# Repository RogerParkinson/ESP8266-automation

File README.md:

ESP8266-automation
==

Code and circuitry to support simple event driven signaling from remote sensors (ESP8266) to a server (BeagleBone) over WIFI. The remote sensors detect an n/o switch being closed and they send a message to the server which decides what to do with it. Normally it logs it and there is a web page to query the log. But for some messages it will sound a chime. The remote sensors also send a battery status when they power up.

I could have used some public service to manage the logging, and eliminated the Beaglebone, but I tend to resist exposing home automation events to public services and I had the Beaglebone already acting as a file server. I'm not sure I would have easily managed the chime from a public service, though probably another ESP listening on the network could do it.

Remote Switch
=

The remote sensors use an ESP8266-01. Use 3xAA batteries as the power supply and any convenient ssensor. A simple mercury switch is fine but I did something more complicated in the one shown in the following image.

The black box is an AA battery holder containing 3 NiMH rechargeable AA batteries. The wires from that are connected to the purple board, the one I designed, and at the other end the ESP8266-01 is plugged in.

The purple board has a test button on it which forces it to send a message. It also has a pair of grey wires going to the n/o switch. A slightly simpler configuration is to solder a mercury switch directly to those connections and make the unit standalone. If you do that make sure you adjust the way the mercury switch is lying to ensure it is open until disturbed. I use that configuration on vermin traps.

This configuration, however, is for my gate. I have a wooden gate on my drive and I rigged a slider on it using some fencing wire, bits of copper and a piece of dowel.

On the right hand side you can see two grey wires. The lower one is fencing wire, quite stiff. That is attached to the gate and provides the movement. The other wire is electrical and is the other end of one of the wires you saw earlier. Its mate is attached to the piece of copper wrapped around the nail. Driven by the fencing wire the dowel slides back and forth and the copper sleeve on the dowel touches the copper on the nail, making the conection. That triggers the ESP to send a signal with it's internal serial number (see the code) to the Beaglebone over WIFI.

I have a similar arrangement on my mailbox, but that is triggered by a mercury switch positioned so that my mail lady's vehicle (she comes in a car because we're rural) runs over a buried metal rod and that jiggles the mercury switch envough to trigger the unit there.
  
The project board is defined in the Eagle files under the ESP8266TX directory. There are connectors on the board for VCC and GND as well as two for the Switch (eg the mercury switch). This switch earths the CH_PD pin on the ESP which will wake it from deep sleep. You can solder the ESP onto it directly but I prefer to use [these connectors](https://www.aliexpress.com/item/50-pcs-4P-4pin-Female-Single-Row-Straight-Header-Strip-Socket-Connector-Pitch-2-54mm/32442780670.html) so I can unplug the ESP if I need to reflash it. Flash the ESP with the code in RemoteSwitch.ino [details here](https://madurasoftware.com/blog/esp8266-01-flashing-tool). There is a note in the top of the ino file explaining how to specify your own WIFI network.

You can order the board ($4 for 3) from [OSH PARK]

<a href="https://www.oshpark.com/shared_projects/U9vJnOx3"></img></a>

It is worth while removing the red LED from the ESP because it runs all the time and reduces battery life. Just grab it with some small pliers and pull.

BeagleBone
=

The server is a Beaglebone running Nginx with some PHP scripts.

To set up the BeagleBone just install [Nginx](https://www.nginx.com/resources/wiki/start/topics/tutorials/install/#) and copy the php scripts from this project into `/usr/share/nginx/www`

If you want to use the chime then you need to wire up the BeagleBone like this:

And arrange for the `BeagleBone/startup/gpio60.sh` script to run at startup.

But better than a breadboard is to use a PCB. You'll find the one I used under BeagleBone/BBConnector in this project. And you can:

<a href="https://www.oshpark.com/shared_projects/K8a6LmDk"></img></a>

All this is doing is taking the 5V supply from the Beaglebone and applying it to the chimer. The chimer I had was part of an old alarm system I had lying around. It took 5V to sound a 'ding-dong' like a door bell. I'm controlling it with the transistor using a 3.3V signal from the Beaglebone GPIO. The transistor I used is a through hole one I happened to have.

Also create a file `/home/receiver/log.csv` and use chmod to make it writeable from anyone. This is the log file and it can be viewed by browsing to `http://<your BeagleBone>/printlog.php`. You should see something like this:

This shows mostly battery levels logged at startup, but the second entry shows the value in red, indicating it has dropped below 3000. The last entry is an actual event on the mailbox and was used to test the chime. I've since added a reboot and test button because sometimes I want to reboot the Beaglebone without trekking all the way upstairs to do it, and the test button triggers the chime without my having to go outside and swing on the gate.

To get the log showing the right names for the devices you need to edit the printlog.php file. Specifically this line:

`$sources = array("test" => "123","pond" => "16058556","backdoor" => "8442031", "mailbox" => "8425573");`

The values it is mapping against are the unique id of each ESP8266 obtained from the `ESP.getChipId()` call. If there is no mapping value the unmapped value appears in the log.

The same thing appears in the processevent.php file where the message source name is used to decide hether to sound the chime or not. You can customise this as needed.

To log the time properly you must ensure the BeagleBone's clock is set correctly. there is help on how to do this [here](http://derekmolloy.ie/automatically-setting-the-beaglebone-black-time-using-ntp/) however I had to use usr/sbin/ntp rather than usr/bin/ntp on my system.

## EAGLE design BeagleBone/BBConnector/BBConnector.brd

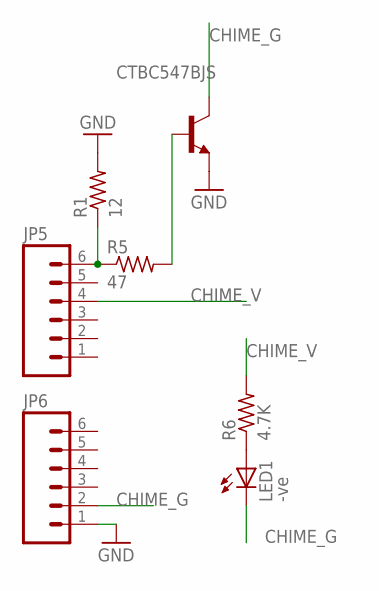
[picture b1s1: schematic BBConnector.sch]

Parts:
CTBC547BJS: 2N2222; TO92-EBC-OVAL
JP5, JP6: M06NO_SILK_YES_STOP; 1X06_NO_SILK_YES_STOP
LED1: -ve; CHIP-LED0603
R1: 12; R0603
R5: 47; R0603
R6: 4.7K; R0603

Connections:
CHIME_G: CTBC547BJS.C, JP6.2, LED1.C
CHIME_V: JP5.4, R6.2
GND: CTBC547BJS.E, JP6.1, R1.2
unnamed: JP5.6, R1.1, R5.1
unnamed: LED1.A, R6.1
unnamed: CTBC547BJS.B, R5.2

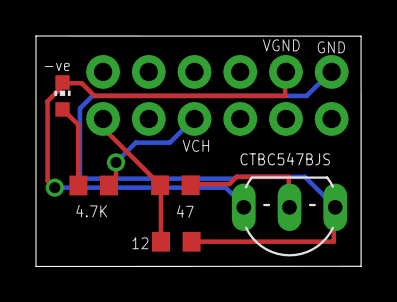
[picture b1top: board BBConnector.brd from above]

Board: 2 copper layers, 18.1 x 12.8 mm, 7 parts (0 on the bottom side), 6 nets.

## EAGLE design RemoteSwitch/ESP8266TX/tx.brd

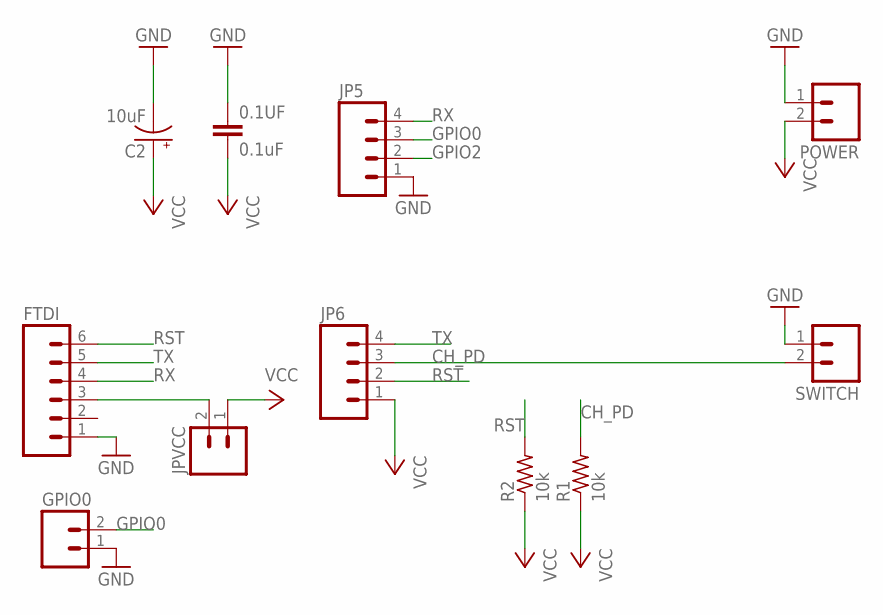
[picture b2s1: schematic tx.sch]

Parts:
0.1UF: 0.1uF; 0603-CAP
C2: 10uF; EIA6032
FTDI: M06LOCK; 1X06_LOCK
GPIO0: M02PTH; 1X02
JP5, JP6: M041X04_NO_SILK; 1X04_NO_SILK
JPVCC: M02PTH; 1X02
POWER: M02PTH; 1X02
R1, R2: 10k; R0805
SWITCH: M02PTH; 1X02

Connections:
CH_PD: JP6.3, R1.2, SWITCH.2
GND: 0.1UF.1, C2.P$2 (-), FTDI.1, GPIO0.1, JP5.1, POWER.1, SWITCH.1
GPIO0: GPIO0.2, JP5.3
GPIO2: JP5.2
unnamed: FTDI.3, JPVCC.2
RST: FTDI.6, JP6.2, R2.2
RX: FTDI.4, JP5.4
TX: FTDI.5, JP6.4
VCC: 0.1UF.2, C2.P$1 (+), JP6.1, JPVCC.1, POWER.2, R1.1, R2.1

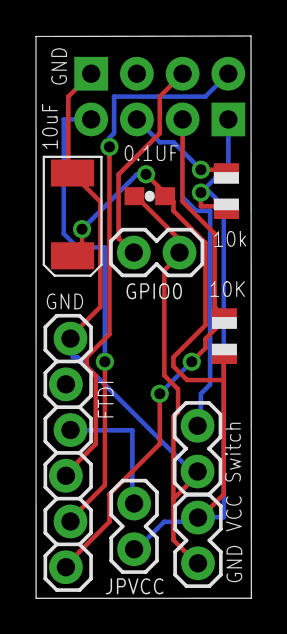
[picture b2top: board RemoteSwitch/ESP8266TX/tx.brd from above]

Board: 2 copper layers, 12.0 x 31.2 mm, 11 parts (0 on the bottom side), 8 nets.

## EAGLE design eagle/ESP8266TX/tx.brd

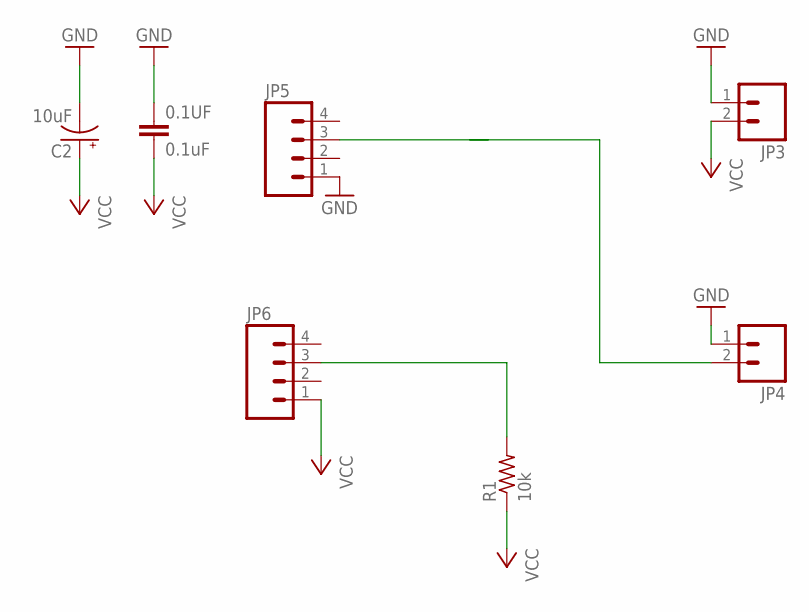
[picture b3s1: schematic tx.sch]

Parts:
0.1UF: 0.1uF; 0603-CAP
C2: 10uF; EIA6032
JP3, JP4: M02PTH; 1X02
JP5, JP6: M041X04_NO_SILK; 1X04_NO_SILK
R1: 10k; R0805

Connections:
GND: 0.1UF.1, C2.P$2 (-), JP3.1, JP4.1, JP5.1
unnamed: JP4.2, JP5.3
unnamed: JP6.3, R1.2
VCC: 0.1UF.2, C2.P$1 (+), JP3.2, JP6.1, R1.1

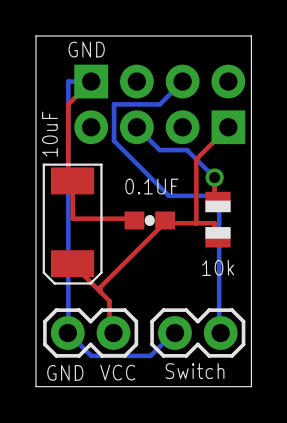
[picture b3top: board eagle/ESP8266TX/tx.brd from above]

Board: 2 copper layers, 12.0 x 19.5 mm, 7 parts (0 on the bottom side), 4 nets.

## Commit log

2016-05-05 Revised to use a single url for processing events and updated the readme file
2016-05-09 Reworked for lower power generic remote sensor
2016-05-09 Renamed Possum Trap to RemoteSwitch because it is generic now
2016-05-09 Minor changes to the readme file
2016-05-17 updated timeout (now = 0 ie forever)
2016-05-17 Fritz file showing breadboard layout for testing ESP8266-01
2016-07-05 Added the project board and documentation.
2018-08-18 Updated readme to show latest version of the project.

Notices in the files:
BeagleBone/BBConnector/BBConnector.brd:
Copyright (C) Roger J Parkinson
RemoteSwitch/ESP8266TX/tx.brd:
(c) 2016 Roger Parkinson
parts and their libraries:
SparkFun-Connectors: Licensing: Creative Commons ShareAlike 4.0 International - https://creativecommons.org/licenses/by-sa/4.0
